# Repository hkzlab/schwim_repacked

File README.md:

# SCHWIM Repacked

## DISCLAIMER

Any use of this project is **under your own responsibility**.
You will be responsible of checking the correct construction and functionality of your board.
By using this project You will agree that I cannot be held responsible if it will destroy any of your devices, damage your computer, burn down your house or whatever.

## Introduction

This board is a SMD-based "replacement" of the (S)IWM for old Macintosh Computers, and is based on the work by [DosFox](https://github.com/DosFox1/Shim-IWM), of which it is just a repackaging in different format.

It implements enough of the logic to pass the initial boot check and allow the computer to continue booting. Floppy drive will not be functional. It is designed to fit in the same space as the original IC.

## Hardware

The board was designed with [KiCad](https://kicad.org/) EDA.

### Bill of Materials

| Component         | Qty | Type / Value                   | Notes                                                    |
| ----------------- | --- | ------------------------------ | -------------------------------------------------------- |
| C1, C2            |  2  | 100nF / 1206 / ceramic         |                                                          |
| U1                |  1  | 74HCT244                       | TSSOP-20                                                 |
| U2                |  1  | 74AHCT1G32                     | SOT-23                                                   |
| RN1, RN2          |  2  | 4x4.7K isolated resistor array | 4x0612 (1206 package)                                    |
| pins              |  2  | 14pin machined strips          | Solder these as pins of the replaced IC on the underside, if you find long enough pins, you can insert them from above, solder them, then snip the top away for a lower profile build |

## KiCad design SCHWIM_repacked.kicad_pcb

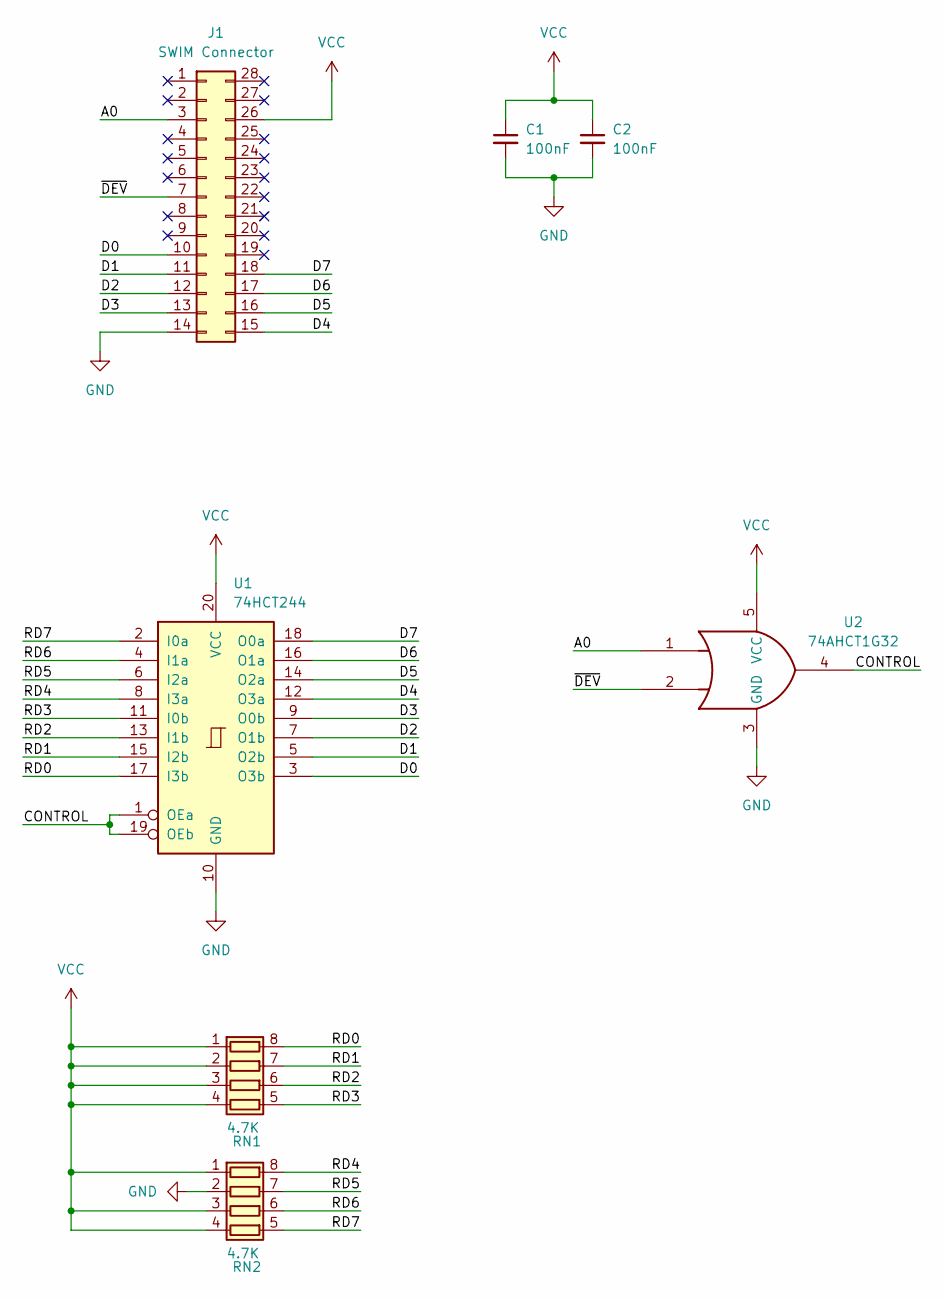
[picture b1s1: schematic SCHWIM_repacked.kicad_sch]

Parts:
C1, C2: 100nF; C_1206_3216Metric_Pad1.33x1.80mm_HandSolder
J1: SWIM Connector; DIP-28_W15.24mm_Socket
RN1, RN2: 4.7K; R_Array_Convex_4x0612
U1: 74HCT244; TSSOP-20_4.4x6.5mm_P0.65mm
U2: 74AHCT1G32; SOT-23-5_HandSoldering

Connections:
/A0: J1.3, U2.1
/CONTROL: U1.1 (OEa), U1.19 (OEb), U2.4
/D0: J1.10, U1.3 (O3b)
/D1: J1.11, U1.5 (O2b)
/D2: J1.12, U1.7 (O1b)
/D3: J1.13, U1.9 (O0b)
/D4: J1.15, U1.12 (O3a)
/D5: J1.16, U1.14 (O2a)
/D6: J1.17, U1.16 (O1a)
/D7: J1.18, U1.18 (O0a)
/RD0: RN1.8 (R1.2), U1.17 (I3b)
/RD1: RN1.7 (R2.2), U1.15 (I2b)
/RD2: RN1.6 (R3.2), U1.13 (I1b)
/RD3: RN1.5 (R4.2), U1.11 (I0b)
/RD4: RN2.8 (R1.2), U1.8 (I3a)
/RD5: RN2.7 (R2.2), U1.6 (I2a)
/RD6: RN2.6 (R3.2), U1.4 (I1a)
/RD7: RN2.5 (R4.2), U1.2 (I0a)
/~DEV: J1.7, U2.2
GND: C1.2, C2.2, J1.14, RN2.2 (R2.1), U1.10 (GND), U2.3 (GND)
VCC: C1.1, C2.1, J1.26, RN1.1 (R1.1), RN1.2 (R2.1), RN1.3 (R3.1), RN1.4 (R4.1), RN2.1 (R1.1), RN2.3 (R3.1), RN2.4 (R4.1), U1.20 (VCC), U2.5 (VCC)

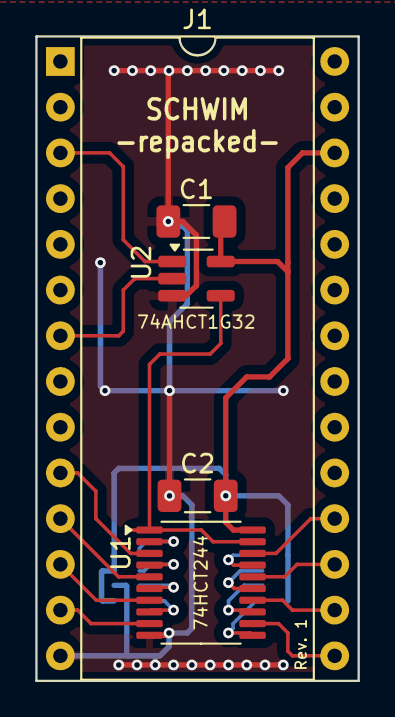
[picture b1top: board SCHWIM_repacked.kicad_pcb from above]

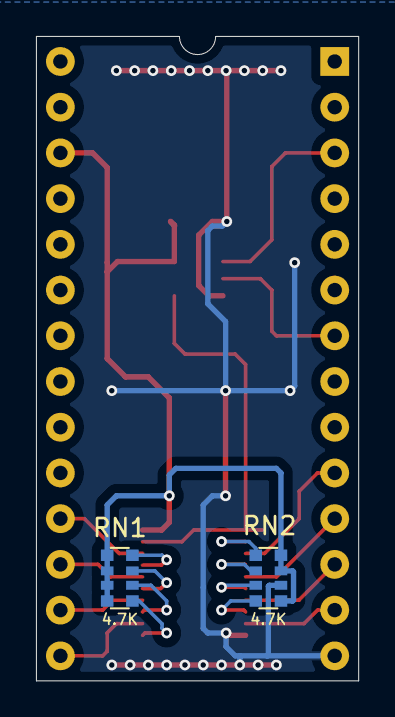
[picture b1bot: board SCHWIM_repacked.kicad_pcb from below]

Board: 2 copper layers, 17.9 x 35.8 mm, 7 parts (2 on the bottom side), 21 nets.

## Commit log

2024-11-01 Add shwim repacked
2024-11-10 Use a single or gate
2024-11-27 Update project
2024-11-27 Better description
2024-12-18 Add better package definition for U2
2024-12-18 Updated schematics
2025-04-20 Added rev.1 of the repacked schwim, fixed footprint for U2
2025-04-20 Update pictures
